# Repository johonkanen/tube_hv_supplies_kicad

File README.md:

# Board renders

Rendered by CI from `johonkanen/tube_hv_supplies_kicad` commit [`8800a549f5`](https://github.com/johonkanen/tube_hv_supplies_kicad/commit/8800a549f57e48c5e9d9b19287351f63d6db6880) on 2026-11-25 06:08 UTC with 10.0.7.
This branch is force-pushed on every render; do not commit to it.

## tube_hv_supplies_rev3 (`rev3/kicad/tube_hv_supplies_rev3.kicad_pcb`)

Copper layers:
- [B_Cu](tube_hv_supplies_rev3/B_Cu.png)
- [F_Cu](tube_hv_supplies_rev3/F_Cu.png)
- [In1_Cu](tube_hv_supplies_rev3/In1_Cu.png)
- [In2_Cu](tube_hv_supplies_rev3/In2_Cu.png)

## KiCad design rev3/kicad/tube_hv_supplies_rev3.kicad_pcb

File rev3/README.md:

# HV supplies rev 3: soft-switched draft (fifth pass, 2026-11-25: one multiplexed converter, 4-layer layout next)

The redesign of the HV supplies board (v2, converted at the repo root, frozen) for the rev B
amplifier: two controllable outputs **V_ANODE** (0 to about 400 V, 0.5 A peak) and **V_SCREEN** (up
to about 390 V, 100 mA average, 0.25 A peak) from the tube PSU's 420-430 V raw rail, the raw HV
distribution to the preamp and PI + FX (two fused RAW_SS feeds), the power star and the fault / RF
network to the chassis. Contract: tube_amplifier_kicad `docs/interfaces.md` (IF-1.1) and
`docs/grounding.md`. rev3/ is its own p2k board root (`p2k_config.py`, PROJECT
`tube_hv_supplies_rev3`); the v2 files at the repo root are not touched.

Status, the second pass decision by decision, the interface check, rail currents, the floorplan
and open questions. Third pass: the accepted L-shaped outline (trimmed at the rear panel), the chosen
floorplan (`mechanical/floorplan_chosen.md`, KiCad outline `mechanical/outline_edge_cuts.kicad_pcb`),
V_ANODE sized for 0.7 A continuous. Simulation pass: the switching model, ramp-down into the PSU,
the power stage on the converter, short / arc, channel change and start-up runs, with the changes
they forced; see: **[STATUS.md](STATUS.md)** (earlier passes kept below it as history).

## Build

```
python3 rev3/tools/make_lib.py          # lib/tube_hv_supplies_rev3.kicad_sym from KiCad's stock libraries (flattened)
python3 rev3/tools/make_footprints.py   # lib/tube_hv_supplies_rev3.pretty (blade tabs, ETD39 inductor), kicad/fp-lib-table
python3 rev3/tools/make_project.py      # project, root sheet, empty sub-sheets
python3 rev3/tools/sheets/draw_all.py   # all five sheets + lib/footprint_map.csv + bom/bom.csv (overwrites them)
tools/p2k/bin/kicad-cli sch erc --severity-all -o rev3/reports/erc.rpt rev3/kicad/tube_hv_supplies_rev3.kicad_sch
cd rev3/sim && python3 lc_ac.py && python3 loop_digital.py && python3 discharge.py   # ngspice + numpy/scipy
cd rev3/sim && python3 r1_turnoff.py && for s in r1_softsw r2_filter r3_damping r4_residue r5_devices r6_sampling r7_fourth_pass; do python3 $s.py; done   # fourth pass
cd rev3/sim && for s in m15_bridge m17_ramp_down m18_power_stage m20_short_arc m21_channel_change m22_startup_failsafe; do python3 $s.py; done
#   (m18 / m21 import the power amp's stage.py from ~/dev/tube_power_amp_kicad read only; a few minutes each)
python3 rev3/mechanical/floorplan_chosen.py   # chosen outline + floorplan, KiCad Edge.Cuts outline
python3 rev3/mechanical/layout_sketch.py     # layout sketch, interfaces only: layout_sketch.png / layout_sketch_routes.png
python3 rev3/mechanical/floorplan.py    # second-pass outline study (history)
```

The sheets are generated: edit `tools/sheets/draw_all.py`, not the `.kicad_sch` files. Drawing style
is netlist-first (parts on a grid, a wire stub and a label on every pin), as in tube_preamp_kicad
rev_b: exact for ERC and the netlist, a tidy layout pass comes later. **ERC: 0 errors, 2 warnings**
(both explained in STATUS.md). 260 parts, 139 nets (fourth pass: TCM bridges on the chassis plate, IF-2.2 fast ADCs). Footprints assigned on every part (stock KiCad
libraries; board-local blade tabs and the custom ETD39 inductor); BOM `bom/bom.csv`
(97 lines, candidate part numbers where chosen, none TBD). No layout.

| Sheet | Contents |
|---|---|
| 01 | J101 raw HV in (B_P / B_N), R101 / R102 link footprints (0 Ω fitted, or 10-47 Ω 2 W fusible) to J102 / J103 (RAW_SS1 / RAW_SS2 with GND_PRE returns), input filter (C101 47 µF, L101 33 µH), raw bleeder 2 x 75 kΩ 2 W and HV-present LED, NT101 (the star point PGND ↔ GND_STAR), fault / RF network (GBU8J ‖ 100 nF Y2 ‖ 100 Ω) to the plated standoff H101 next to J101; H102-H106 non-plated. No brake |
| 02 | Two synchronous bucks in triangular-current mode (40-150 kHz): IKP08N65F5 lying on the chassis plate (aluminium bars, 1.5 mm Al2O3), 220 pF snubbers, 220 / 470 µH ETD39 N97, C1 100 µF (+ 4.7 µF film on bridge 1) through the I_C shunt, second stage 68 µH / 4.7 µF film / 22 µF + 1.0 Ω leg (8.9 kHz), ULW5 fusibles standing, D201, J201 / J202 |
| 03 | One UCC21520 per bridge (200 ns dead-time floor, per-edge dead time from the FPGA), bootstrap, 15 Ω / 10 kΩ gate parts |
| 04 | Fifth pass: V_ANODE / V_SCREEN / RAW dividers and buffers, four OPA2836 current amplifiers (50 mohm Kelvin shunts in the low-side emitters and capacitor negatives), TMUX1308 8:1 multiplexer stepped by a 74LVC163 on CS_FAST, OPA2836 driver, one ADS7056, REF3030 3.0 V |
| 05 | J1 (IF-2.3 proposed), HV_PERMIT loop input, DIS = NAND(HV_PERMIT, HV_ENABLE); no comparators, no latch (fifth pass) |

## Layout

```
rev3/
  p2k_config.py          board root for the p2k tools
  tools/make_lib.py      symbol library from KiCad's stock libraries
  tools/make_project.py  project skeleton
  tools/make_footprints.py  board-local footprints
  tools/sheets/draw_all.py  the five sheets, footprint map, BOM
  lib/                   generated symbol library, footprints, footprint_map.csv
  kicad/                 generated KiCad 10 project
  bom/bom.csv            first BOM (refs, value, footprint, candidate part number)
  reports/erc.rpt        ERC report
  sim/                   hvnet.py (shared network), lc_ac.py, loop_digital.py, discharge.py and their
                         *_results.md; converter_avg.py (first pass, brake cases superseded);
                         swmodel.py + m15/m17/m18/m20/m21/m22_*.py (simulation pass) with results and plots
  mechanical/            floorplan.py, floorplan.md, floorplan_*.svg
```

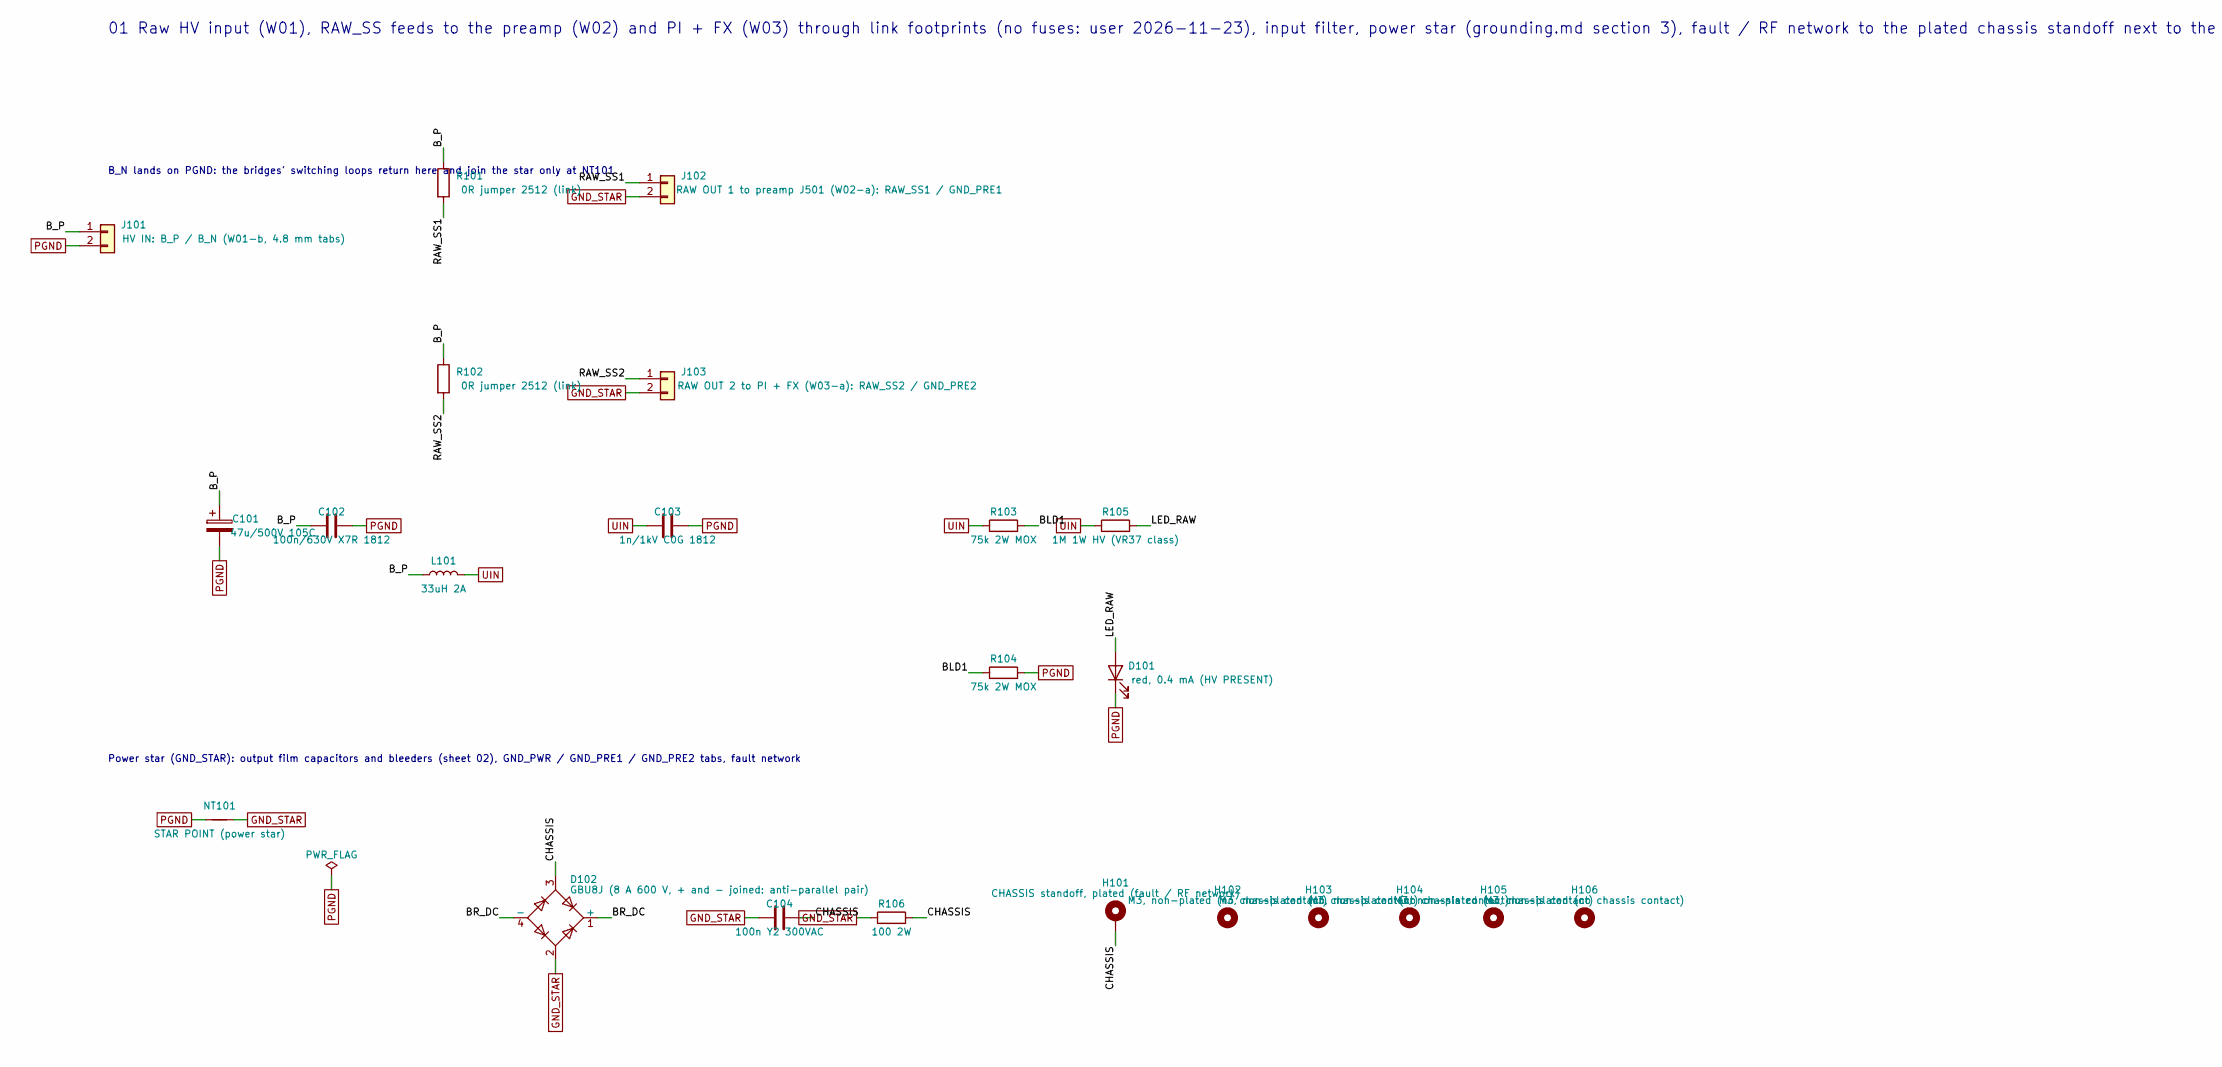
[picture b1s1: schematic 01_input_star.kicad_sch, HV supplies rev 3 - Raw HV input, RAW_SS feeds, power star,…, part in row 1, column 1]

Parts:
C101: 47u/500V 105C; CP_Radial_D18.0mm_P7.50mm
C102: 100n/630V X7R 1812; C_1812_4532Metric
C103: 1n/1kV C0G 1812; C_1812_4532Metric
C104: 100n Y2 300VAC; C_Rect_L26.5mm_W8.5mm_P22.50mm_MKS4; MPN TDK B32023A3104M
D101: red, 0.4 mA (HV PRESENT); LED_0805_2012Metric
D102: GBU8J (8 A 600 V, + and - joined: anti-parallel p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; Diode_Bridge_Vishay_GBU; MPN GBU8J
H101: CHASSIS standoff, plated (fault / RF network); MountingHole_3.2mm_M3_DIN965_Pad
H102, H103, H104, H105, H106: M3, non-plated (no chassis contact); MountingHole_3.2mm_M3
J101: HV IN: B_P / B_N (W01-b, 4.8 mm tabs); Blade_Tab_4.8mm_2x_P12mm
J102: RAW OUT 1 to preamp J501 (W02-a): RAW_SS1 / GND_P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; Blade_Tab_4.8mm_2x_P12mm
J103: RAW OUT 2 to PI + FX (W03-a): RAW_SS2 / GND_PRE2; Blade_Tab_4.8mm_2x_P12mm
L101: 33uH 2A; L_Radial_D12.0mm_P5.00mm_Fastron_11P
NT101: STAR POINT (power star); NetTie-2_SMD_Pad2.0mm
R101, R102: 0R jumper 2512 (link); R_2512_6332Metric
R103, R104: 75k 2W MOX; R_Axial_DIN0617_L17.0mm_D6.0mm_P20.32mm_Horizontal
R105: 1M 1W HV (VR37 class); R_Axial_DIN0414_L11.9mm_D4.5mm_P15.24mm_Horizontal
R106: 100 2W; R_Axial_DIN0617_L17.0mm_D6.0mm_P20.32mm_Horizontal

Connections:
/01 Raw HV input, RAW_SS feeds (links), power star, fault network, bleeder/BLD1: R103.2, R104.1
/01 Raw HV input, RAW_SS feeds (links), power star, fault network, bleeder/BR_DC: D102.1 (+), D102.4 (-)
/01 Raw HV input, RAW_SS feeds (links), power star, fault network, bleeder/B_P: C101.1, C102.1, J101.1, L101.1, R101.1, R102.1
/01 Raw HV input, RAW_SS feeds (links), power star, fault network, bleeder/CHAS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: C104.2, D102.3, H101.1, R106.2
/01 Raw HV input, RAW_SS feeds (links), power star, fault network, bleeder/LED_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: D101.2 (A), R105.2
/01 Raw HV input, RAW_SS feeds (links), power star, fault network, bleeder/RAW_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: J102.1, R101.2
/01 Raw HV input, RAW_SS feeds (links), power star, fault network, bleeder/RAW_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: J103.1, R102.2
GND_STAR: C104.1, D102.2, J102.2, J103.2, NT101.2, R106.1; also elsewhere on the board
PGND: C101.2, C102.2, C103.2, D101.1 (K), J101.2, NT101.1, R104.2; also elsewhere on the board
UIN: C103.1, L101.2, R103.1, R105.1; also elsewhere on the board

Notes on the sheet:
01 Raw HV input (W01), RAW_SS feeds to the preamp (W02) and PI + FX (W03) through link footprints (no fuses: user 2026-11-23), input filter, power star (grounding.md section 3), fault / RF network to the plated chassis standoff next to the raw input tabs, raw bleeder and HV indicator. No brake: the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
B_N lands on PGND: the bridges' switching loops return here and join the star only at NT101
Power star (GND_STAR): output film capacitors and bleeders (sheet 02), GND_PWR / GND_PRE1 / GND_PRE2 tabs, fault network

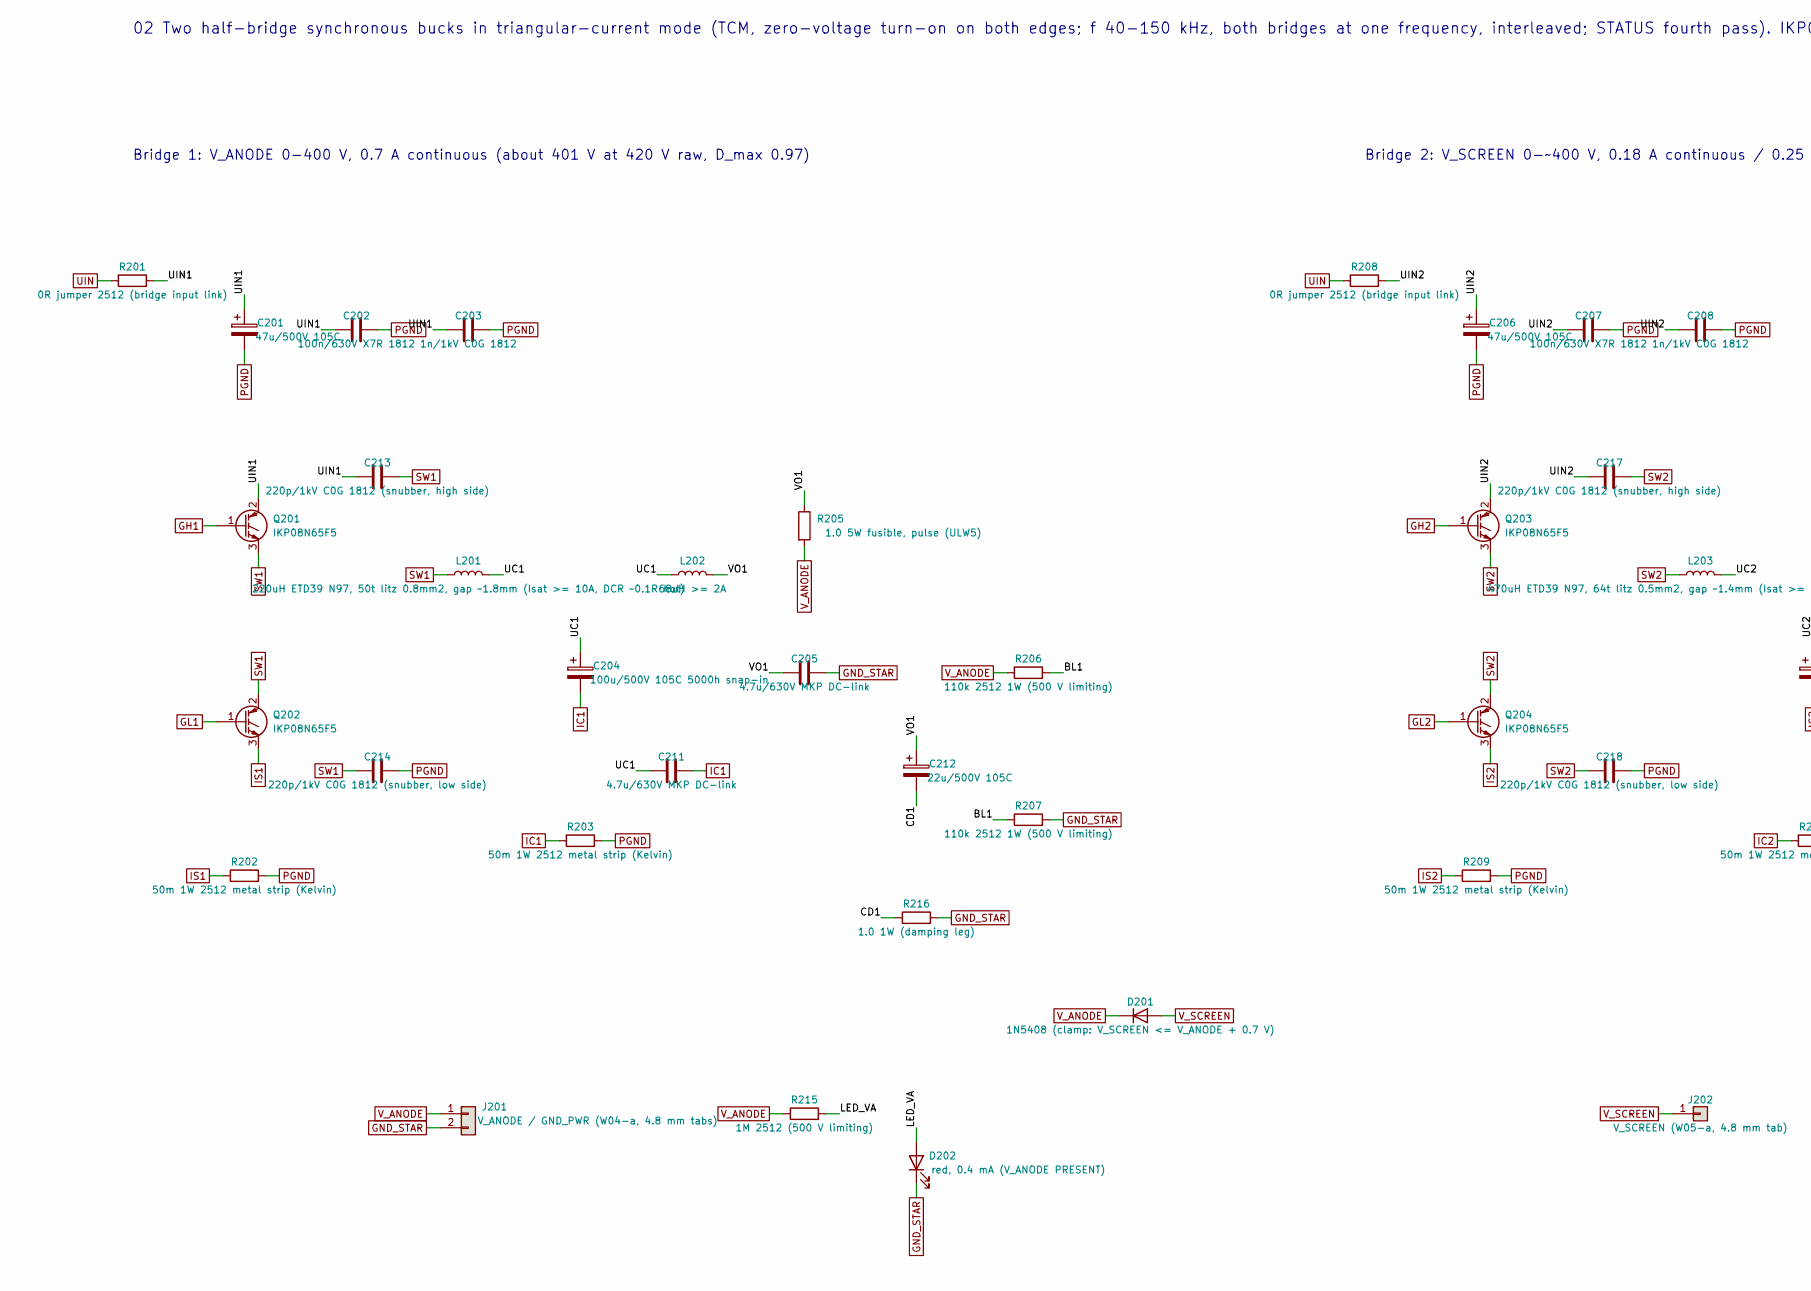
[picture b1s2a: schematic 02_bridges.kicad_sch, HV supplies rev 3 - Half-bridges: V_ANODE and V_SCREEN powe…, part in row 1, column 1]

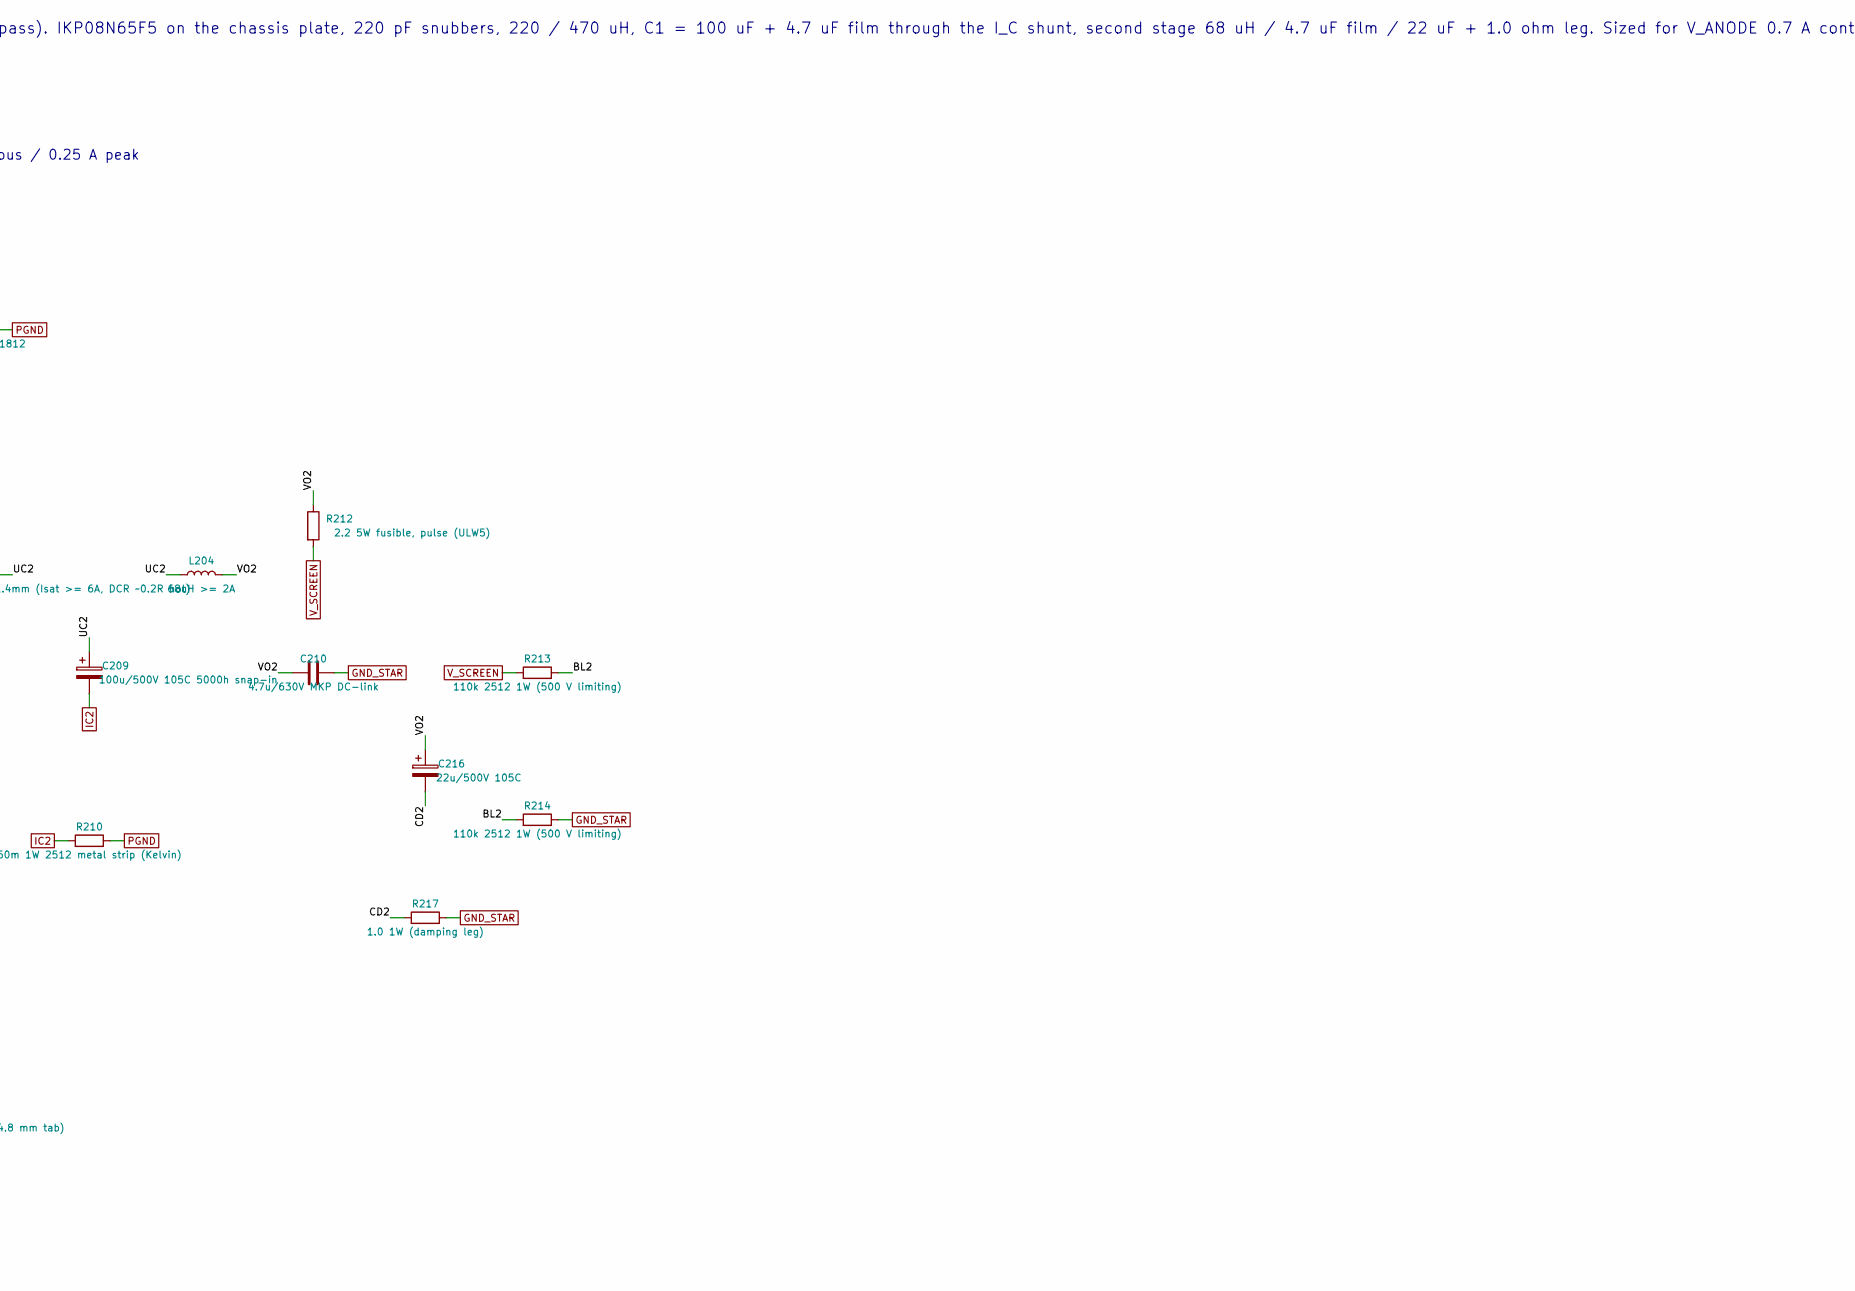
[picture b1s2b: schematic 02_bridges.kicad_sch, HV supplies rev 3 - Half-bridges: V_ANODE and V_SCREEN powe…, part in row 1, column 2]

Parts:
C201, C206: 47u/500V 105C; CP_Radial_D18.0mm_P7.50mm
C202, C207: 100n/630V X7R 1812; C_1812_4532Metric
C203, C208: 1n/1kV C0G 1812; C_1812_4532Metric
C204, C209: 100u/500V 105C 5000h snap-in; CP_Radial_D22.0mm_P10.00mm_SnapIn; MPN Vishay MAL215919101E3 (PUL-SI, 22 x 40)
C205, C210, C211: 4.7u/630V MKP DC-link; C_Rect_L31.5mm_W17.0mm_P27.50mm_MKS4; MPN TDK B32674D6475K
C212, C216: 22u/500V 105C; CP_Radial_D16.0mm_P7.50mm
C213, C217: 220p/1kV C0G 1812 (snubber, high side); C_1812_4532Metric
C214, C218: 220p/1kV C0G 1812 (snubber, low side); C_1812_4532Metric
D201: 1N5408 (clamp: V_SCREEN <= V_ANODE + 0.7 V); D_DO-201AD_P5.08mm_Vertical_CathodeUp; MPN 1N5408
D202: red, 0.4 mA (V_ANODE PRESENT); LED_0805_2012Metric
J201: V_ANODE / GND_PWR (W04-a, 4.8 mm tabs); Blade_Tab_4.8mm_2x_P12mm
J202: V_SCREEN (W05-a, 4.8 mm tab); Blade_Tab_4.8mm_1x
L201: 220uH ETD39 N97, 50t litz 0.8mm2, gap ~1.8mm (Isa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; L_ETD39_2pin_custom; MPN TDK B66363G0000X197 (N97) core set + ET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
L202, L204: 68uH >= 2A; L_Radial_D16.8mm_P11.43mm_Vishay_IHB-1; MPN Vishay IHB-1 68 uH (current rating to c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
L203: 470uH ETD39 N97, 64t litz 0.5mm2, gap ~1.4mm (Isa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; L_ETD39_2pin_custom; MPN TDK B66363G0000X197 (N97) core set + ET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
Q201, Q202, Q203, Q204: IKP08N65F5; TO-220-3_Horizontal_TabUp_Bar; MPN IKP08N65F5XKSA1
R201, R208: 0R jumper 2512 (bridge input link); R_2512_6332Metric
R202, R203, R209, R210: 50m 1W 2512 metal strip (Kelvin); R_2512_6332Metric; MPN Vishay WSL2512R0500FEA
R205: 1.0 5W fusible, pulse (ULW5); R_Axial_DIN0918_L18.0mm_D9.0mm_P7.62mm_Vertical; MPN TT Welwyn ULW5-1R0J (ordering suffix to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
R206, R207, R213, R214: 110k 2512 1W (500 V limiting); R_2512_6332Metric; MPN Vishay CRCW2512 class (to confirm)
R212: 2.2 5W fusible, pulse (ULW5); R_Axial_DIN0918_L18.0mm_D9.0mm_P7.62mm_Vertical; MPN TT Welwyn ULW5-2R2J (ordering suffix to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
R215: 1M 2512 (500 V limiting); R_2512_6332Metric
R216, R217: 1.0 1W (damping leg); R_Axial_DIN0414_L11.9mm_D4.5mm_P7.62mm_Vertical

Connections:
/02 Half-bridges: V_ANODE and V_SCREEN power stages/BL1: R206.2, R207.1
/02 Half-bridges: V_ANODE and V_SCREEN power stages/BL2: R213.2, R214.1
/02 Half-bridges: V_ANODE and V_SCREEN power stages/CD1: C212.2, R216.1
/02 Half-bridges: V_ANODE and V_SCREEN power stages/CD2: C216.2, R217.1
/02 Half-bridges: V_ANODE and V_SCREEN power stages/LED_VA: D202.2 (A), R215.2
/02 Half-bridges: V_ANODE and V_SCREEN power stages/UC1: C204.1, C211.1, L201.2, L202.1
/02 Half-bridges: V_ANODE and V_SCREEN power stages/UC2: C209.1, L203.2, L204.1
/02 Half-bridges: V_ANODE and V_SCREEN power stages/UIN1: C201.1, C202.1, C203.1, C213.1, Q201.2 (C), R201.2
/02 Half-bridges: V_ANODE and V_SCREEN power stages/UIN2: C206.1, C207.1, C208.1, C217.1, Q203.2 (C), R208.2
/02 Half-bridges: V_ANODE and V_SCREEN power stages/VO1: C205.1, C212.1, L202.2, R205.1
/02 Half-bridges: V_ANODE and V_SCREEN power stages/VO2: C210.1, C216.1, L204.2, R212.1
GH1: Q201.1 (G); also elsewhere on the board
GH2: Q203.1 (G); also elsewhere on the board
GL1: Q202.1 (G); also elsewhere on the board
GL2: Q204.1 (G); also elsewhere on the board
GND_STAR: C205.2, C210.2, D202.1 (K), J201.2, R207.2, R214.2, R216.2, R217.2; also elsewhere on the board
IC1: C204.2, C211.2, R203.1; also elsewhere on the board
IC2: C209.2, R210.1; also elsewhere on the board
IS1: Q202.3 (E), R202.1; also elsewhere on the board
IS2: Q204.3 (E), R209.1; also elsewhere on the board
PGND: C201.2, C202.2, C203.2, C206.2, C207.2, C208.2, C214.2, C218.2, R202.2, R203.2, R209.2, R210.2; also elsewhere on the board
SW1: C213.2, C214.1, L201.1, Q201.3 (E), Q202.2 (C); also elsewhere on the board
SW2: C217.2, C218.1, L203.1, Q203.3 (E), Q204.2 (C); also elsewhere on the board
UIN: R201.1, R208.1; also elsewhere on the board
V_ANODE: D201.1 (K), J201.1, R205.2, R206.1, R215.1; also elsewhere on the board
V_SCREEN: D201.2 (A), J202.1, R212.2, R213.1; also elsewhere on the board

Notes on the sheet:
02 Two half-bridge synchronous bucks in triangular-current mode (TCM, zero-voltage turn-on on both edges; f 40-150 kHz, both bridges at one frequency, interleaved; STATUS fourth pass). IKP08N65F5 on the chassis plate, 220 pF snubbers, 220 / 470 uH, C1 = 100 uF + 4.7 uF film through the I_C shunt, s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
Bridge 1: V_ANODE 0-400 V, 0.7 A continuous (about 401 V at 420 V raw, D_max 0.97)
Bridge 2: V_SCREEN 0-~400 V, 0.18 A continuous / 0.25 A peak

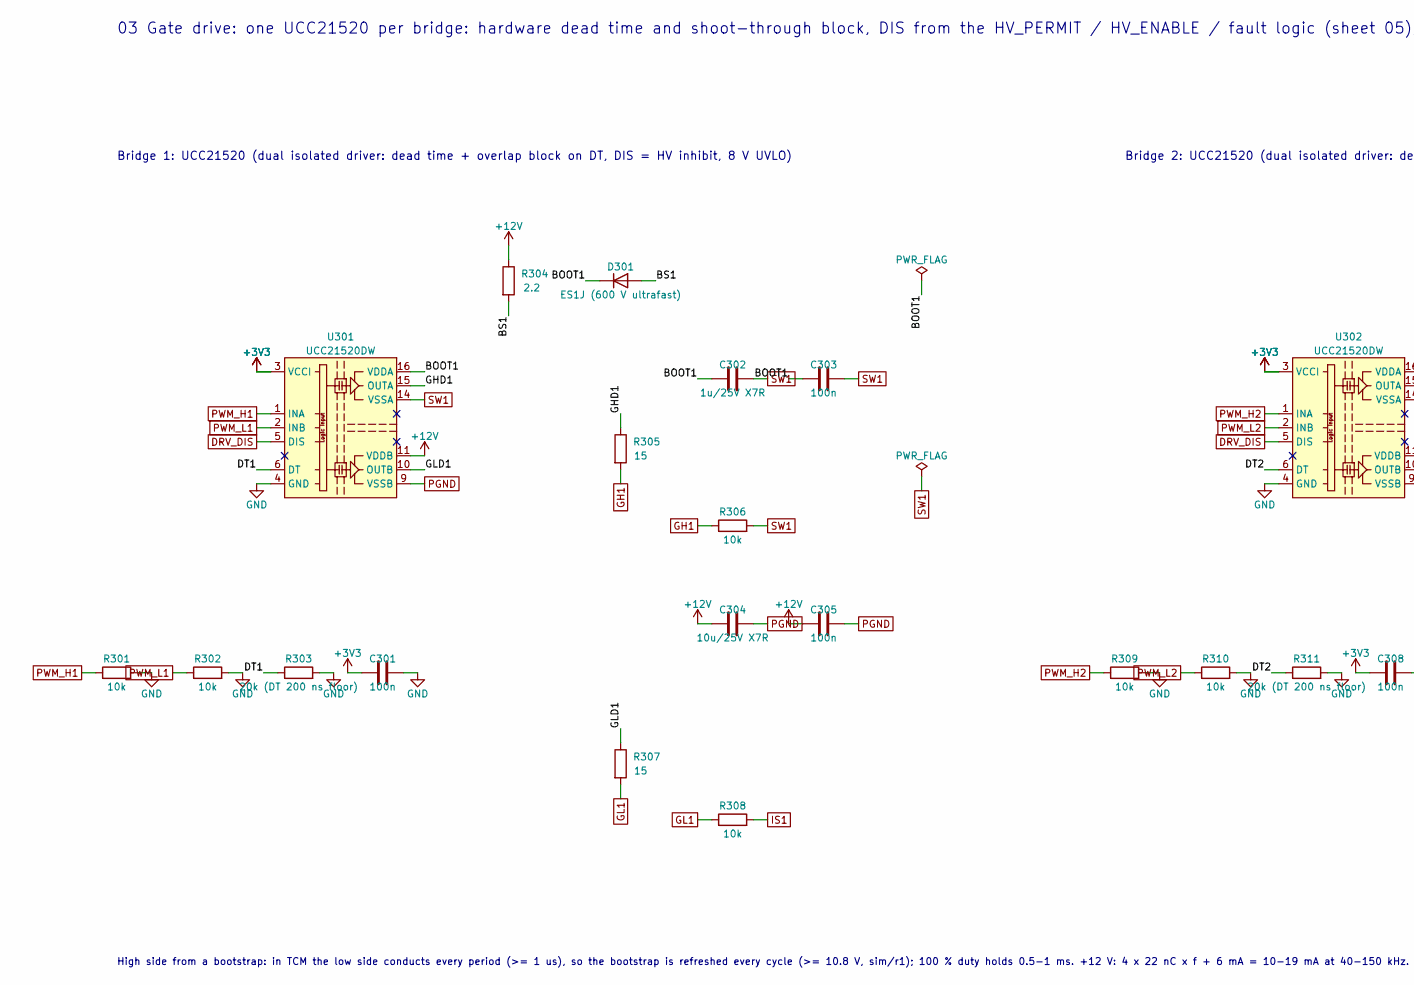
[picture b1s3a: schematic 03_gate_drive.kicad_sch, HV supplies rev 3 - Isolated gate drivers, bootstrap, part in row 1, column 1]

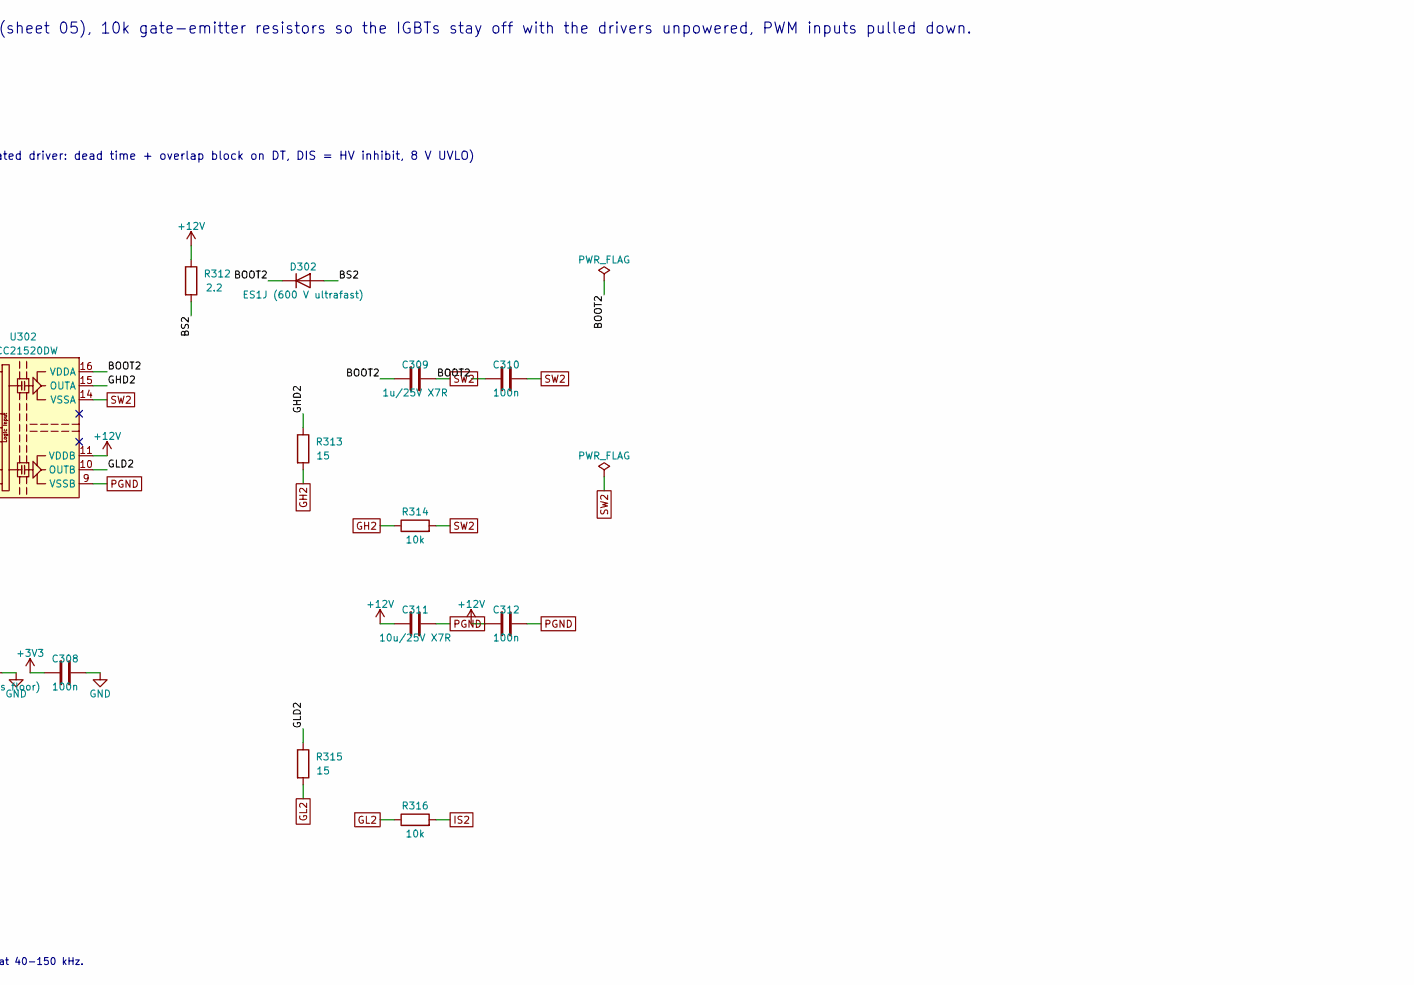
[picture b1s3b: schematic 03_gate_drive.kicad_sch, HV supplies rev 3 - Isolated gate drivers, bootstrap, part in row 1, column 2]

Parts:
C301, C303, C305, C308, C310, C312: 100n; C_0603_1608Metric
C302, C309: 1u/25V X7R; C_0805_2012Metric
C304, C311: 10u/25V X7R; C_1206_3216Metric
D301, D302: ES1J (600 V ultrafast); D_SMA; MPN ES1J
R301, R302, R306, R308, R309, R310, R314, R316: 10k; R_0603_1608Metric
R303, R311: 20k (DT 200 ns floor); R_0603_1608Metric
R304, R312: 2.2; R_0603_1608Metric
R305, R307, R313, R315: 15; R_0805_2012Metric
U301, U302: UCC21520DW; SOIC-16W_7.5x10.3mm_P1.27mm; MPN UCC21520DWR

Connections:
+3V3: C301.1, C308.1, U301.3 (VCCI), U301.8 (VCCI), U302.3 (VCCI), U302.8 (VCCI); also elsewhere on the board
+12V: C304.1, C305.1, C311.1, C312.1, R304.1, R312.1, U301.11 (VDDB), U302.11 (VDDB); also elsewhere on the board
/03 Isolated gate drivers, bootstrap/BOOT1: C302.1, C303.1, D301.1 (K), U301.16 (VDDA)
/03 Isolated gate drivers, bootstrap/BOOT2: C309.1, C310.1, D302.1 (K), U302.16 (VDDA)
/03 Isolated gate drivers, bootstrap/BS1: D301.2 (A), R304.2
/03 Isolated gate drivers, bootstrap/BS2: D302.2 (A), R312.2
/03 Isolated gate drivers, bootstrap/DT1: R303.1, U301.6 (DT)
/03 Isolated gate drivers, bootstrap/DT2: R311.1, U302.6 (DT)
/03 Isolated gate drivers, bootstrap/GHD1: R305.1, U301.15 (OUTA)
/03 Isolated gate drivers, bootstrap/GHD2: R313.1, U302.15 (OUTA)
/03 Isolated gate drivers, bootstrap/GLD1: R307.1, U301.10 (OUTB)
/03 Isolated gate drivers, bootstrap/GLD2: R315.1, U302.10 (OUTB)
DRV_DIS: U301.5 (DIS), U302.5 (DIS); also elsewhere on the board
GH1: R305.2, R306.1; also elsewhere on the board
GH2: R313.2, R314.1; also elsewhere on the board
GL1: R307.2, R308.1; also elsewhere on the board
GL2: R315.2, R316.1; also elsewhere on the board
GND: C301.2, C308.2, R301.2, R302.2, R303.2, R309.2, R310.2, R311.2, U301.4 (GND), U302.4 (GND); also elsewhere on the board
IS1: R308.2; also elsewhere on the board
IS2: R316.2; also elsewhere on the board
PGND: C304.2, C305.2, C311.2, C312.2, U301.9 (VSSB), U302.9 (VSSB); also elsewhere on the board
PWM_H1: R301.1, U301.1 (INA); also elsewhere on the board
PWM_H2: R309.1, U302.1 (INA); also elsewhere on the board
PWM_L1: R302.1, U301.2 (INB); also elsewhere on the board
PWM_L2: R310.1, U302.2 (INB); also elsewhere on the board
SW1: C302.2, C303.2, R306.2, U301.14 (VSSA); also elsewhere on the board
SW2: C309.2, C310.2, R314.2, U302.14 (VSSA); also elsewhere on the board

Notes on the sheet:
03 Gate drive: one UCC21520 per bridge: hardware dead time and shoot-through block, DIS from the HV_PERMIT / HV_ENABLE / fault logic (sheet 05), 10k gate-emitter resistors so the IGBTs stay off with the drivers unpowered, PWM inputs pulled down.
Bridge 1: UCC21520 (dual isolated driver: dead time + overlap block on DT, DIS = HV inhibit, 8 V UVLO)
Bridge 2: UCC21520 (dual isolated driver: dead time + overlap block on DT, DIS = HV inhibit, 8 V UVLO)
High side from a bootstrap: in TCM the low side conducts every period (>= 1 us), so the bootstrap is refreshed every cycle (>= 10.8 V, sim/r1); 100 % duty holds 0.5-1 ms. +12 V: 4 x 22 nC x f + 6 mA = 10-19 mA at 40-150 kHz.
